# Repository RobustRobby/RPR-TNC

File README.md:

1. Introduction
The first design of a Teensy-based TNC as a replacement for the SCS Tracker was conceived by Peter Mack and Hans-Peter Helfert, DL6MAA, of SCS. It was based on a stack of a Teensy 4.0 board on top of an audio shield, which was itself on top of a piece of generic PCB for holding some components like a PTT transistor and some LEDs. Soon however, the stack of three PCBs was found to be sub-optimal and the idea of designing a custom PCB came into existence. Peter designed a first version of such a custom PCB, but lacked the time to finish it.

2. The present design
The present design was made by Robert, DM4RW, starting from the initial design of Peter. It is made using KiCad, now in version 7 (note that earlier versions of KiCad cannot open files saved in KiCad 7 format). The idea of the design revolves around putting the SGTL5000 sound chip (the same as used on the audio shield) together will all other components required on a main PCB, no longer requiring the use of an audio shield. Also the Teensy 4.0 micro-controller board finds a place on the main PCB, slightly elevated so as to allow space for components directly under the Teensy.

3. The PCB
The PCB provides space for the SGTL5000 sound chip plus its supporting components, a GPS/GNSS module, connectors such as SMA for an antenna for GPS/GNSS and mini-DIN-6 for connecting a transceiver, signaling LEDs, a 3,5mm RST socket for auxiliary use and a push button to initiate firmware updates. In addition, the design provides for its own power supply allowing power to be provided via pin 5 of the mini-DIN-6 socket as well as PTT via separate PTT line and via the audio-out line (the latter can be activated with a jumper).

4. Specifics of the design
The GNSS module used so far is a Quectel LC76. This is not obligatory, any GPS/GNSS module having the same pin-out and having the same physical size can be used, as long as its (serial) interface to the Teensy runs with 9k6 bps. A simple power back-up arrangement was made, using an over-sized capacitor. This will not allow the GNSS module to continue to run for a long time, but it at least bridges shorter interruptions of the power supply. The LC76 automatically recognizes whether the antenna needs power or not, and deactivates power if there is something wrong the antenna line or the antenna. The Teensy uses an unshielded processor. The external antenna is therefore a requirement and should be put away from the PCB as far as possible, preferably with a free sight to the skies.

The SGTL5000 sound chip finds its place beneath the Teensy. It is the 20 (21) pin version, as opposed to the 32 pin version used on the audio shield. However, the 32 pin version has been discontinued, the 20 pin version not. Note that the chip is very small: it measures 4×4mm with 5 pins on each side, plus a 21st pin on the bottom. There is no means of soldering this by hand, a decent re-flow installation is the least you need to put it into place.

The 3,5mm RST socket is meant to support auxiliary services. As to the date of writing, no firmware supporting such services in a flawless manner has been issued. The RST socket may therefore be omitted, it does not change the behavior of the TNC in any way.

The on-board power supply accepts input voltages between 8 and 28 volts on pin 5 of the mini-DIN-6 socket, and reduces this to 5 volts for the Teensy. It is based on a step-down converter by TI, the TPS54202(H). It is important to note that this converter comes in two flavors, with the H at the end and without. The only difference is the “enable voltage”. The one needs a high voltage, the other a low. For the H version, resistor R13 must be omitted, otherwise the converter won’t start. For the flavor without the H, resistor R13 has to be on the board. Simple measures were taken to prevent current flowing in an uncontrolled manner from computer to external power supply or vice versa in case the Teensy is connected to USB AND external power. However, for that to work, the Teensy must be slightly modified in that the trace connecting the power coming from the USB to the main 5v rail on the Teensy is interrupted (see the Teensy documentation that comes with every Teensy). It is then bridged by a diode that is on the PCB. If you do not need an external power supply, all components related to the power supply can be safely omitted. In that case, powering the TNC can only be done via USB connected to the Teensy.

5. About the files
You’ll find the KiCad files which you can open with the freely available KiCad. At least version 7 should be used, or higher. But not lower, that won’t work. You’ll find Gerber files with which the PCBs can be produced. Furthermore there is a BOM (bill of materials) and P&P (pick-and-placement) files. These were generated to have the board produced by JLCPCB and in addition to that, have all SMD components soldered on the board by JLCPCB. Only the GNSS module and wired components must then be soldered in order to get a fully charged RPR TNC. However, you can choose any other service provider that does the same, although in that case you’d be surely advised to regenerate all files according to the instructions of that service provider. Also with JLCPCB it pays off to check whether their requirements have changed and if so, regenerate all files.

Robert, DM4RW (Meersburg, 07/05/2024)

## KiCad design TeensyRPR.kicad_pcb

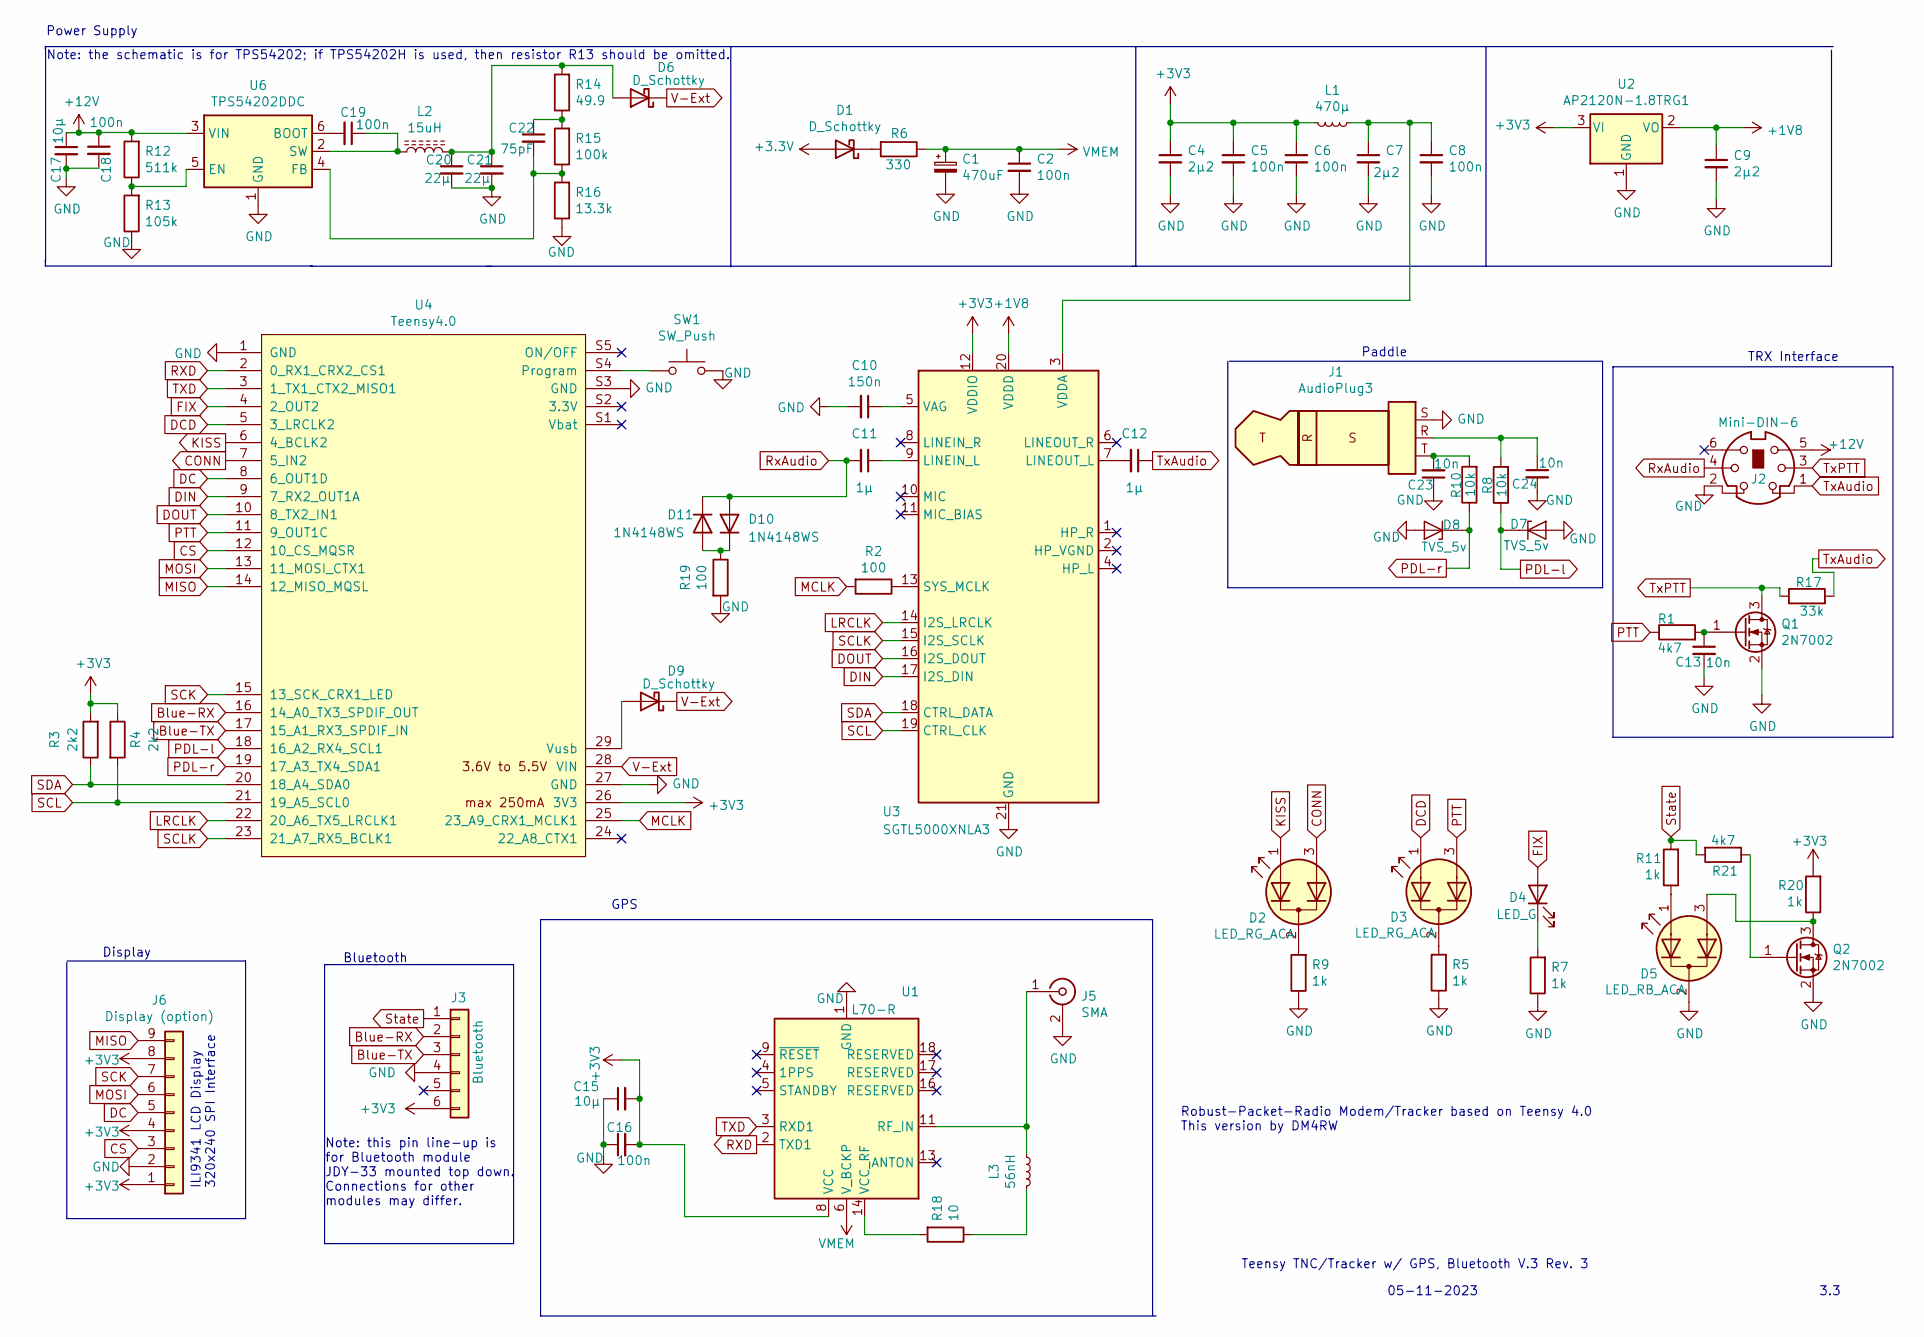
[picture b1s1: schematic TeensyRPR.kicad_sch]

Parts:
C1: 470uF; CP_Elec_6.3x7.7; LCSC C114446
C2, C5, C6, C8, C16, C18, C19: 100n; C_0402_1005Metric; LCSC C307331
C4, C7, C9: 2µ2; C_1206_3216Metric; LCSC C50254
C10: 150n; C_0805_2012Metric; LCSC C307539
C11, C12: 1µ; C_0805_2012Metric; LCSC C28323
C13, C23, C24: 10n; C_0402_1005Metric; LCSC C15195
C15, C17: 10µ; C_0805_2012Metric; LCSC C15850
C20, C21: 22µ; C_0603_1608Metric; LCSC C2992620
C22: 75pF; C_0603_1608Metric; LCSC C282074
D1, D6, D9: D_Schottky; D_SOD-123; LCSC C8598
D2, D3: LED_RG_ACA; LED_D3.0mm-3
D4: LED_G; LED_D3.0mm
D5: LED_RB_ACA; LED_D3.0mm-3
D7, D8: TVS_5v; D_SOD-323; LCSC C85200
D10, D11: 1N4148WS; D_SOD-323; LCSC C108805
J1: AudioPlug3; Jack_3.5mm_Switronic_ST-005-G_horizontal
J2: Mini-DIN-6; Mini_DIN_6_TE_Connectivity
J3: Bluetooth; PinHeader_1x06_P2.54mm_Vertical
J5: SMA; SMA_Molex_73251-2200_Horizontal
J6: Display (option); PinHeader_1x09_P2.54mm_Vertical
L1: 470µ; L_1210_3225Metric; LCSC C295109
L2: 15uH; L_Taiyo-Yuden_MD-3030; LCSC C222856
L3: 56nH; L_0402_1005Metric; LCSC C27143
Q1, Q2: 2N7002; SOT-23; LCSC C916396
R1, R21: 4k7; R_0603_1608Metric; LCSC C23162
R2, R19: 100; R_0603_1608Metric; LCSC C22775
R3, R4: 2k2; R_0603_1608Metric; LCSC C4190
R5, R7, R9, R11, R20: 1k; R_0603_1608Metric; LCSC C253329
R6: 330; R_0603_1608Metric; LCSC C23138
R8, R10: 10k; R_0603_1608Metric; LCSC C23179
R12: 511k; R_0603_1608Metric; LCSC C101089
R13: 105k; R_0603_1608Metric; LCSC C141685
R14: 49.9; R_0603_1608Metric; LCSC C114625
R15: 100k; R_0603_1608Metric; LCSC C465461
R16: 13.3k; R_0603_1608Metric; LCSC C234280
R17: 33k; R_Axial_DIN0204_L3.6mm_D1.6mm_P2.54mm_Vertical
R18: 10; R_2010_5025Metric; LCSC C458682
SW1: SW_Push; SW_Tactile_SPST_Angled_PTS645Vx31-2LFS
U1: L70-R; Quectel_L70-R; LCSC C2916232
U2: AP2120N-1.8TRG1; SOT-23; LCSC C460317
U3: SGTL5000XNLA3; SGTL5000-QFN-20-1EP_3x3mm_P0.4mm_ThermalVias; LCSC C2651833
U4: Teensy4.0; Teensy40-DIP-28_W15.24mm
U6: TPS54202DDC; SOT-23-6; LCSC C191884

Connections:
+1V8: C9.1, U2.2 (VO), U3.20 (VDDD)
+12V: C17.1, C18.1, J2.5, R12.2, U6.3 (VIN)
Blue-RX: J3.2, U4.16 (14_A0_TX3_SPDIF_OUT)
Blue-TX: J3.3, U4.17 (15_A1_RX3_SPDIF_IN)
CONN: D2.3 (A2), U4.7 (5_IN2)
CS: J6.3, U4.12 (10_CS_MQSR)
DC: J6.5, U4.8 (6_OUT1D)
DCD: D3.1 (A1), U4.5 (3_LRCLK2)
DIN: U3.17 (I2S_DIN), U4.9 (7_RX2_OUT1A)
DOUT: U3.16 (I2S_DOUT), U4.10 (8_TX2_IN1)
FIX: D4.2 (A), U4.4 (2_OUT2)
GND: C1.2, C2.2, C4.2, C5.2, C6.2, C7.2, C8.2, C9.2, C10.2, C13.2, C15.1, C16.1, C17.2, C18.2, C20.2, C21.2, C23.1, C24.2, D5.2 (K), D7.2 (A2), D8.2 (A2), J1.S, J2.2, J3.4, J5.2 (Ext), J6.2, Q1.2 (S), Q2.2 (S), R5.1, R7.1, R9.1, R13.1, R16.1, R19.2, SW1.2, U1.1 (GND), U1.10 (GND), U1.12 (GND), U2.1 (GND), U3.21 (GND), U4.1 (GND), U4.27 (GND), U4.S3 (GND), U6.1 (GND)
KISS: D2.1 (A1), U4.6 (4_BCLK2)
LRCLK: U3.14 (I2S_LRCLK), U4.22 (20_A6_TX5_LRCLK1)
MCLK: R2.2, U4.25 (23_A9_CRX1_MCLK1)
MISO: J6.9, U4.14 (12_MISO_MQSL)
MOSI: J6.6, U4.13 (11_MOSI_CTX1)
unnamed: C22.1, R14.1, R15.2
unnamed: C23.2, J1.T, R10.2
unnamed: C24.1, J1.R, R8.2
unnamed: D1.1 (K), R6.2
unnamed: D2.2 (K), R9.2
unnamed: D3.2 (K), R5.2
unnamed: D4.1 (K), R7.2
unnamed: D5.1 (A1), R11.1
unnamed: D5.3 (A2), Q2.3 (D), R20.1
unnamed: C20.1, C21.1, D6.2 (A), L2.2, R14.2
unnamed: D9.2 (A), U4.29 (Vusb)
unnamed: D10.1 (K), D11.2 (A), R19.1
unnamed: J5.1 (In), L3.1, U1.11 (RF_IN)
unnamed: L3.2, R18.1
unnamed: C13.1, Q1.1 (G), R1.2
unnamed: Q2.1 (G), R21.1
unnamed: R18.2, U1.14 (VCC_RF)
unnamed: C11.1, U3.9 (LINEIN_L)
unnamed: C12.2, U3.7 (LINEOUT_L)
unnamed: R2.1, U3.13 (SYS_MCLK)
unnamed: C10.1, U3.5 (VAG)
unnamed: C7.1, C8.1, L1.1, U3.3 (VDDA)
unnamed: SW1.1, U4.S4 (Program)
unnamed: C19.2, U6.6 (BOOT)
unnamed: R12.1, R13.2, U6.5 (EN)
unnamed: C22.2, R15.1, R16.2, U6.4 (FB)
unnamed: C19.1, L2.1, U6.2 (SW)
PDL-l: D7.1 (A1), R8.1, U4.18 (16_A2_RX4_SCL1)
PDL-r: D8.1 (A1), R10.1, U4.19 (17_A3_TX4_SDA1)
PTT: D3.3 (A2), R1.1, U4.11 (9_OUT1C)
RXD: U1.2 (TXD1), U4.2 (0_RX1_CRX2_CS1)
RxAudio: C11.2, D10.2 (A), D11.1 (K), J2.4
SCK: J6.7, U4.15 (13_SCK_CRX1_LED)
SCL: R4.2, U3.19 (CTRL_CLK), U4.21 (19_A5_SCL0)
SCLK: U3.15 (I2S_SCLK), U4.23 (21_A7_RX5_BCLK1)
SDA: R3.1, U3.18 (CTRL_DATA), U4.20 (18_A4_SDA0)
State: J3.1, R11.2, R21.2
TXD: U1.3 (RXD1), U4.3 (1_TX1_CTX2_MISO1)
TxAudio: C12.1, J2.1, R17.2
TxPTT: J2.3, Q1.3 (D), R17.1
V-Ext: D6.1 (K), D9.1 (K), U4.28 (VIN)
VMEM: C1.1, C2.1, R6.1, U1.6 (V_BCKP)

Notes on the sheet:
Bluetooth
Robust-Packet-Radio Modem/Tracker based on Teensy 4.0 This version by DM4RW
ILI9341 LCD Display 320x240 SPI Interface
3.3
Teensy TNC/Tracker w/ GPS, Bluetooth V.3 Rev. 3
Power Supply
05-11-2023
TRX Interface
Display
GPS
Paddle
Note: this pin line-up is for Bluetooth module JDY-33 mounted top down. Connections for other modules may differ.
Note: the schematic is for TPS54202; if TPS54202H is used, then resistor R13 should be omitted.

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
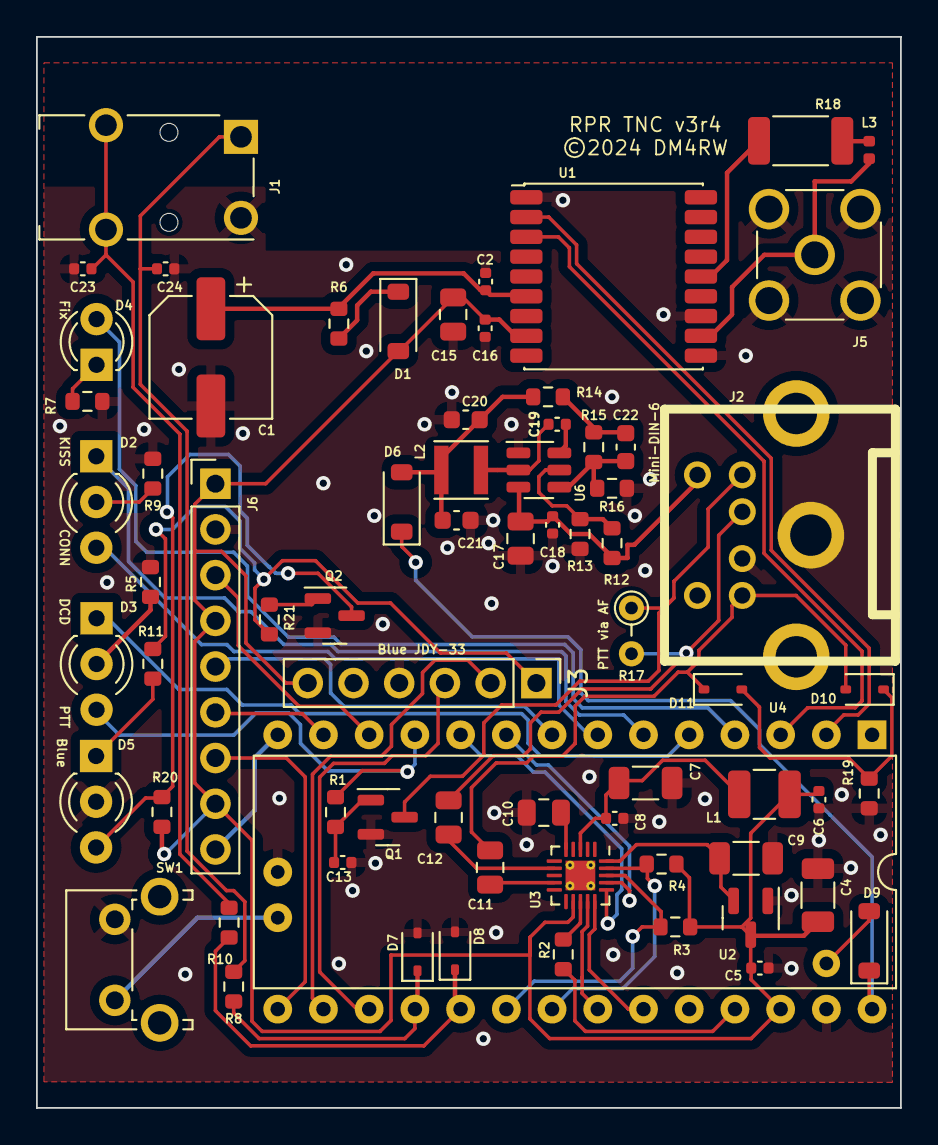
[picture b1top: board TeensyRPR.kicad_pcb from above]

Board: 2 copper layers, 48.0 x 59.5 mm, 70 parts (0 on the bottom side), 60 nets.

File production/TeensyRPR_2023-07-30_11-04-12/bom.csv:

Designator,Footprint,Quantity,Value,LCSC Part #
C1,CP_Elec_6.3x7.7,1,470uF,C114446
C10,805,1,150n,C307539
"C11, C12",805,2,1µ,C28323
"C13, C23, C24",402,3,10n,C15195
"C15, C17",805,2,10µ,C15850
"C16, C18, C19, C5, C6, C8",402,6,100n,C307331
C2,402,1,100nF,C307331
"C20, C21",603,2,22µ,C2991805
C22,603,1,75pF,C282074
"C4, C7, C9",1206,3,2µ2,C50254
"D1, D6, D9",D_SOD-123,3,D_Schottky,C8598
"D10, D11",D_SOD-323,2,1N4148WS,C108805
"D7, D8",D_SOD-323,2,TVS_5v,C170167
L1,1210,1,470µ,C295109
L2,L_Taiyo-Yuden_MD-3030,1,15uH,C222856
L3,402,1,56nH,C27143
Q1,SOT-23,1,2N7002,C65189
R1,603,1,4k7,C23162
"R10, R8",603,2,10k,C23179
"R11, R5, R7, R9",603,4,470,C23179
R12,603,1,511k,C101089
R13,603,1,105k,C100713
R14,603,1,49.9,C114625
R15,603,1,100k,C465461
R16,603,1,13.3k,C234280
R17,603,1,33k,C4216
R18,2010,1,10,C458682
"R19, R2",603,2,100,C22775
"R3, R4",603,2,2k2,C4190
R6,603,1,330,C23138
U1,Quectel_L70-R,1,L70-R,C2916232
U2,SOT-23,1,AP2120N-1.8TRG1,C460317 
U3,SGTL5000-QFN-20-1EP_3x3mm_P0.4mm_ThermalVias,1,SGTL5000XNLA3,C2651833
U6,SOT-23-6,1,TPS54202DDC,C191884

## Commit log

2024-05-15 Create LICENSE

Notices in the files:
TeensyRPR.kicad_pcb:
©2024 DM4RW
